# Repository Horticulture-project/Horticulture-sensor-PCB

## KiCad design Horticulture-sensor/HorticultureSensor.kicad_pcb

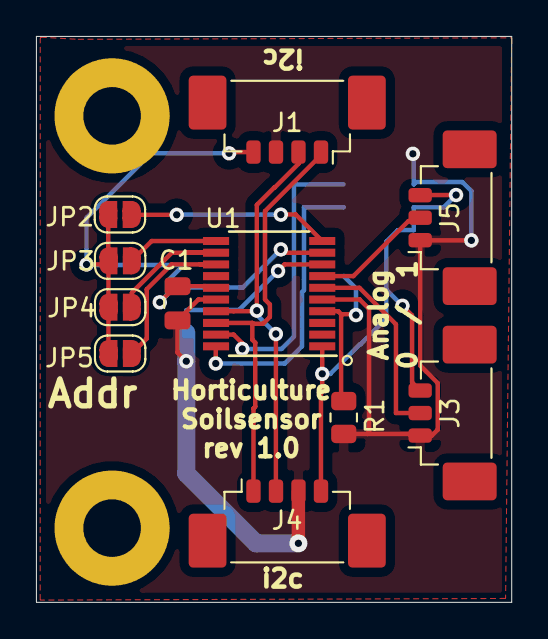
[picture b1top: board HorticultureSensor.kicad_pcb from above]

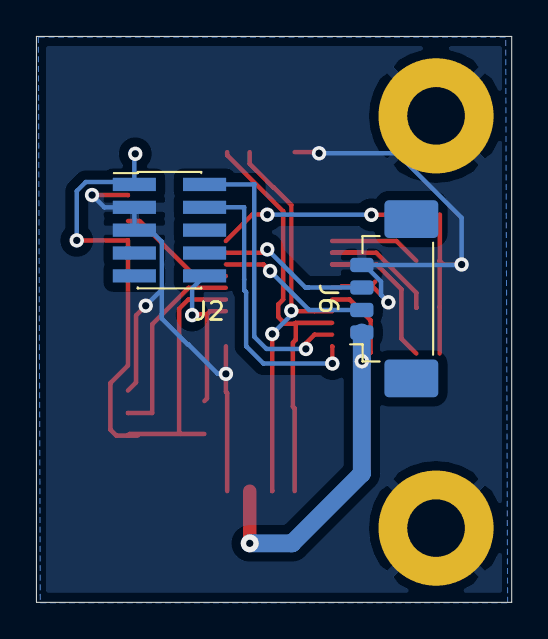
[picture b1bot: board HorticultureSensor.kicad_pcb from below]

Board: 2 copper layers, 26.4 x 31.4 mm, 15 parts (2 on the bottom side), 15 nets.

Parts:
C1: 100nF; C_0805_2012Metric
H1, H2: MountingHole_Pad; MountingHole_3.2mm_M3_Pad
J1, J4, J6: Conn_01x04; Molex_PicoBlade_53398-0471_1x04-1MP_P1.25mm_Vertical
J2: Conn_02x05_Odd_Even; PinHeader_2x05_P1.27mm_Vertical_SMD
J3, J5: Conn_01x03; Molex_PicoBlade_53398-0371_1x03-1MP_P1.25mm_Vertical
JP2, JP3, JP4, JP5: SolderJumper_2_Open; SolderJumper-2_P1.3mm_Open_RoundedPad1.0x1.5mm
R1: 10k2; R_0805_2012Metric
U1: STM32F030F4Px; TSSOP-20_4.4x6.5mm_P0.65mm

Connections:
+3V3: C1.1, J1.3, J2.1, J3.1, J4.3, J5.1, J6.1, R1.1, U1.5, U1.16
AnalogSignal0: J3.2, U1.6
AnalogSignal1: J5.2, U1.7
GND: C1.2, H1.1, H2.1, J1.4, J2.3, J2.5, J3.3, J4.4, J5.3, J6.4, JP2.2, JP3.2, JP4.2, JP5.2, U1.1, U1.15
I2c-SCL: J1.2, J4.2, U1.17
I2c-SDA: J1.1, J4.1, U1.18
SWD-SWCLK: J2.4, U1.20
SWD-SWIO: J2.2, U1.19
UART-rx: J6.3, U1.9
UART-tx: J6.2, U1.8
i2c-addr_0: JP2.1, U1.10
i2c-addr_1: JP3.1, U1.11
i2c-addr_2: JP4.1, U1.12
i2c-addr_3: JP5.1, U1.13
nRESET: J2.10, R1.2, U1.4

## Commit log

2020-11-28 Board file
2020-12-03 Resolves #4 #6 #5
2020-12-03 Resolves #3, Resolves #6, Resolves #5
2020-12-03 Added BOM
2020-12-03 Resolves #2
2020-12-06 Completed routing
    Soilsensor rev 1.0
2020-12-06 Created plots
2020-12-06 Updated BOM
